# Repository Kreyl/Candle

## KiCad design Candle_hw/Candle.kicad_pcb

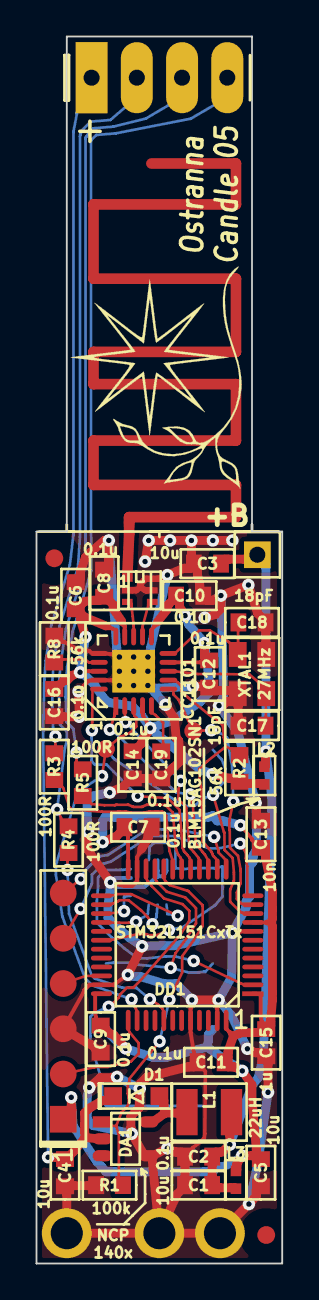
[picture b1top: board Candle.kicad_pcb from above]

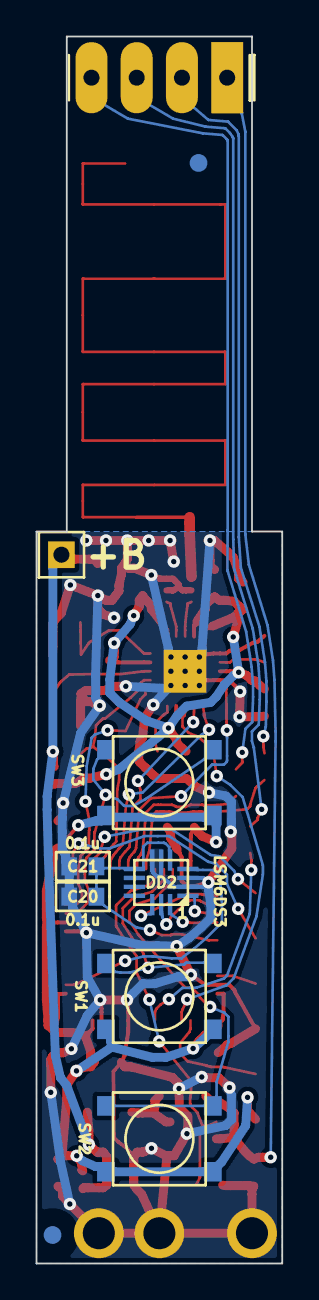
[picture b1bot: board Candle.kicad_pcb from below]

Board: 2 copper layers, 13.8 x 68.9 mm, 54 parts (8 on the bottom side), 39 nets.

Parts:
ANT1: ANT_PCB_MONO; ANT_868_10d4x36
BLN1: BALUN868JOHANSON; BALUN_JOHANSON868
C1, C3, C4, C5: 10u; CAP_0603
C2, C6, C7, C8, C9, C10, C11, C12, C14, C16, C19, C20, C21: 0.1u; CAP_0603
C13: 10n; CAP_0603
C15: 1u; CAP_0603
C17, C18: 18pF; CAP_0603
D1: BAT54WS; SOD323
DA1: NCP1400; SOT23-5
DD1: STM32L151CxTx; LQFP48
DD2: LSM6DS3; 14_3x2d5_p0d5
DD3: CC1101; QFN20
L1: 22uH; IND_1210_LQH32C
L2, L3: BLM15AG102SN1; IND_0402
Logo1: Logo; Ostranna_12d7_10d1
R1: 100k; RES_0603
R2, R8: 56k; RES_0603
R3, R4, R5: 100R; RES_0603
RP1, RP2, RP3, RP4: REFPOINT; REF_POINT_1MM
SW1, SW2, SW3: BUTTON; BTN_4x4_SMD
TP1, TP2: TESTPOINT; TESTPOINT_1MM
XL1: CONN_6; PLS-6-NoHole
XL2: CONN_1; PLS-1Square
XL3, XL4, XL5: CONN_1; SIL1_ROUND_1MM8
XL6: CONN_4; PLS-4-Long
XTAL1: 27MHz; 03225C4

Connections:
+3.3V: C4.2, D1.C, DA1.2, XL6.1
+BATT: C1.2, C2.2, C3.2, L1.2, L2.2, L3.2, XL2.1
/ACC_CS: DD1.25, DD2.12
/ACC_INT1: DD1.2, DD2.4
/ACC_MISO: DD1.27, DD2.1
/ACC_MOSI: DD1.28, DD2.14
/ACC_PWR: C20.1, C21.1, DD1.30, DD2.5, DD2.8
/ACC_SCK: DD1.26, DD2.13
/ANT1: ANT1.1, BLN1.1
/BLUE_LED: DD1.18, R5.2
/CC_CS: DD1.14, DD3.7, R2.1
/CC_GDO0: DD1.11, DD3.6, TP1.1
/CC_GDO2: DD1.38, DD3.3, TP2.1
/CC_MISO: DD1.16, DD3.2
/CC_MOSI: DD1.17, DD3.20
/CC_SCK: DD1.15, DD3.1
/GREEN_LED: DD1.41, R4.2
/LED_EN: DA1.1, DD1.20, R1.1
/Lout: D1.A, DA1.5, L1.1
/RED_LED: DD1.19, R3.2
/RF1: BLN1.4, DD3.12
/RF2: BLN1.3, DD3.13
/SWCLK: DD1.37, XL1.2
/SWDIO: DD1.34, XL1.4
/UART_RX: DD1.13, XL1.6
/UART_TX: DD1.12, XL1.5
GND: BLN1.2, BLN1.5, BLN1.6, C1.1, C2.1, C3.1, C4.1, C5.1, C6.2, C7.2, C8.2, C9.2, C10.2, C11.2, C12.2, C13.2, C14.2, C15.2, C16.2, C17.2, C18.2, C19.1, C20.2, C21.2, DA1.4, DD1.8, DD1.23, DD1.35, DD1.44, DD1.47, DD2.2, DD2.3, DD2.6, DD2.7, DD3.16, DD3.19, DD3.PAD, R1.2, R8.2, XL1.3, XL3.1, XL4.1, XL5.1, XTAL1.H
unnamed: C17.1, DD3.8, XTAL1.1
unnamed: C18.1, DD3.10, XTAL1.2
unnamed: C19.2, DD3.5
unnamed: DD1.10, SW3.1
unnamed: DD1.21, SW1.1
unnamed: DD1.22, SW2.1
unnamed: DD3.17, R8.1
unnamed: R3.1, XL6.2
unnamed: R4.1, XL6.3
unnamed: R5.1, XL6.4
PwrMCU: C5.2, C7.1, C9.1, C11.1, C13.1, C15.1, DD1.1, DD1.9, DD1.24, DD1.36, DD1.48, L3.1, SW1.2, SW2.2, SW3.2, XL1.1
VCC: C6.1, C8.1, C10.1, C12.1, C14.1, C16.1, DD3.4, DD3.9, DD3.11, DD3.14, DD3.15, DD3.18, L2.1, R2.2

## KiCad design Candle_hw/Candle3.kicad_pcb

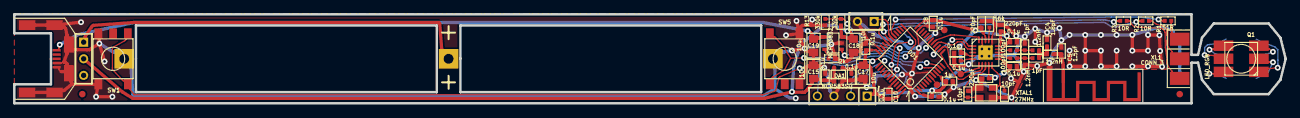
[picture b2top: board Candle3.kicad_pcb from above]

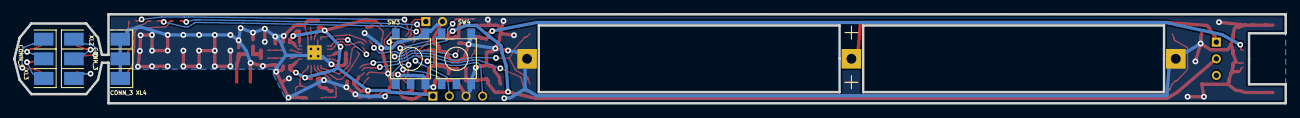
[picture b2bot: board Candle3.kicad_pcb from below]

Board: 2 copper layers, 194.4 x 13.6 mm, 63 parts (5 on the bottom side), 43 nets.

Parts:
ANT1: ANT_GENERAL; ANT_2400_MEANDER
C1, C3: 100pF; CAP_0402
C2, C6: 1pF; CAP_0402
C4: 1.8pF; CAP_0402
C5: 1.5pF; CAP_0402
C7, C13: 10pF; CAP_0402
C8, C9, C10, C11, C14, C16, C41, C51, C111, C141: 0.1u; CAP_0402
C12: 1u; CAP_0402
C15, C17, C18, C19: 10u; CAP_0805
C91, C151, C181: 220pF; CAP_0402
DA1: NCP583SQ; SC82AB
DA2: MCP73832; SOT23-5
DD1: STM32F100C4; LQFP48
DD2: CC2500; QFN20
L1, L2, L3: 1.2nH; IND_0402
Q1: LED_RGB; LED_HH5050_RGB
R1: 51R; RES_0402
R2, R3: 10R; RES_0402
R4: 2k; RES_0402
R6, R13: 330k; RES_0402
R171: 56k; RES_0402
RP1, RP2, RP3: REFPOINT; REF_POINT_1MM
SW1: SWITCH; SIL-3
SW2, SW3, SW4, SW5: BUTTON; BUTTON_6x6SMD
TP1, TP2: TESTPOINT; TESTPOINT_1MM
XL1, XL2, XL3, XL4: CONN_3; CONN_SOLDER3
XL5: ST_SWD; SIL-4
XL6: USB_MICRO_B; USBmicro_MOLEX_WM17142
XL7: CONN_2; SIL-2
XL9, XL15, XL16: CONN_1; SIL1_SQUARE_1MM5
XTAL1: 27MHz; CRYSTAL_03225C4

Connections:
+3.3V: C8.1, C9.1, C10.1, C11.1, C12.1, C16.1, C17.1, C41.1, C91.1, C111.1, C141.1, C151.1, C181.1, DA1.3, DD1.1, DD1.9, DD1.24, DD1.36, DD1.48, DD2.4, DD2.9, DD2.11, DD2.14, DD2.15, DD2.18, XL5.1
+5V: C19.1, DA2.4, XL6.1
+BATT: C14.1, C15.1, C18.1, DA1.1, DA1.4, DA2.3, R6.1, SW1.2
/Ant1: C1.1, DD2.12
/Ant2: C3.1, DD2.13
/BATTERY_PLUS: SW1.1, XL9.1
/BTN_DOWN: DD1.43, SW4.2
/BTN_PWR: DD1.10, SW2.2
/BTN_TX: DD1.11, SW5.2
/BTN_UP: DD1.42, SW3.2
/CC_CS: DD1.13, DD2.7
/CC_GDO0: DD1.14, DD2.6, TP1.1
/CC_MISO: DD1.16, DD2.2
/CC_MOSI: DD1.17, DD2.20
/CC_SCK: DD1.15, DD2.1
/Charge: DA2.1, DD1.25
/LED_B: DD1.32, R3.1
/LED_G: DD1.31, R2.1
/LED_R: DD1.29, R1.1
/SWCLK: DD1.37, XL5.2
/SWDIO: DD1.34, XL5.4
GND: ANT1.2, C4.2, C5.2, C6.2, C7.2, C8.2, C9.2, C10.2, C11.2, C12.2, C13.2, C14.2, C15.2, C16.2, C17.2, C18.2, C19.2, C41.2, C51.2, C91.2, C111.2, C141.2, C151.2, C181.2, DA1.2, DA2.2, DD1.8, DD1.23, DD1.35, DD1.44, DD1.47, DD2.16, DD2.19, DD2.PAD, L1.1, R4.2, R13.2, R171.2, SW2.1, SW3.1, SW4.1, SW5.1, XL4.1, XL4.2, XL4.3, XL5.3, XL6.4, XL6.5, XL6.SHLD, XL7.2, XL15.1, XL16.1, XTAL1.H
unnamed: DA2.5, R4.1
unnamed: Q1.RA, XL2.1
unnamed: Q1.GC, XL3.2
unnamed: Q1.RC, XL3.1
unnamed: Q1.BC, XL3.3
unnamed: Q1.GA, XL2.2
unnamed: Q1.BA, XL2.3
unnamed: R1.2, XL1.1
unnamed: R2.2, XL1.2
unnamed: R3.2, XL1.3
unnamed: C1.2, C2.1, L1.2
unnamed: DD1.7, TP2.1
unnamed: C3.2, C6.1, L3.2
unnamed: ANT1.1, C5.1, L2.1
unnamed: C2.2, C4.1, L2.2, L3.1
unnamed: DD1.30, XL7.1
unnamed: C13.1, DD2.10, XTAL1.2
unnamed: C7.1, DD2.8, XTAL1.1
unnamed: DD1.18, R6.2, R13.1
unnamed: DD2.17, R171.1
unnamed: C51.1, DD2.5

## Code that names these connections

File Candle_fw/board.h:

/*
 * board.h
 *
 *  Created on: 12 ñåíò. 2015 ã.
 *      Author: Kreyl
 */

#pragma once

#include <inttypes.h>

// ==== General ====
#define BOARD_NAME          "Candle05"
#define APP_NAME            "Candle_TxAcg"

// ==== High-level peripery control ====
#define BUTTONS_ENABLED         TRUE

#define SIMPLESENSORS_ENABLED   BUTTONS_ENABLED

// MCU type as defined in the ST header.
#define STM32L151xB

#define SYS_TIM_CLK         (Clk.APB1FreqHz)
#define I2C1_ENABLED        FALSE
#define I2C_USE_SEMAPHORE   FALSE
#define ADC_REQUIRED        FALSE

#if 1 // ========================== GPIO =======================================
// PortMinTim_t: GPIO, Pin, Tim, TimChnl, invInverted, omPushPull, TopValue
// UART
#define UART_GPIO       GPIOA
#define UART_TX_PIN     2
#define UART_RX_PIN     3

// LED
#define LED_EN_PIN      { GPIOB, 2, omPushPull }
#define LED_R_PIN       { GPIOB, 5, TIM3, 2, invInverted, omOpenDrain, 255 }
#define LED_G_PIN       { GPIOB, 0, TIM3, 3, invInverted, omOpenDrain, 255 }
#define LED_B_PIN       { GPIOB, 1, TIM3, 4, invInverted, omOpenDrain, 255 }

// Buttons
#define BTN_TX_PIN      GPIOA, 0, pudPullDown
#define BTN_UP_PIN      GPIOB, 10, pudPullDown
#define BTN_DOWN_PIN    GPIOB, 11, pudPullDown

#define BTN_TX_INDX     0
#define BTN_UP_INDX     1
#define BTN_DOWN_INDX   2

// Acc
#define ACG_IRQ_PIN     GPIOC, 13
#define ACG_CS_PIN      GPIOB, 12
#define ACG_SCK_PIN     GPIOB, 13, omPushPull, pudNone, AF5
#define ACG_MISO_PIN    GPIOB, 14, omPushPull, pudNone, AF5
#define ACG_MOSI_PIN    GPIOB, 15, omPushPull, pudNone, AF5
#define ACG_PWR_PIN     GPIOA, 9
#define ACG_SPI         SPI2

// Radio: SPI, PGpio, Sck, Miso, Mosi, Cs, Gdo0
#define CC_Setup0       SPI1, GPIOA, 5,6,7, 4, 1

#endif // GPIO

#if ADC_REQUIRED // ======================= Inner ADC ==========================
// Clock divider: clock is generated from the APB2
#define ADC_CLK_DIVIDER     adcDiv2

// ADC channels
//#define BAT_CHNL          1

#define ADC_VREFINT_CHNL    17  // All 4xx, F072 and L151 devices. Do not change.
#define ADC_CHANNELS        { ADC_VREFINT_CHNL }
#define ADC_CHANNEL_CNT     1   // Do not use countof(AdcChannels) as preprocessor does not know what is countof => cannot check
#define ADC_SAMPLE_TIME     ast96Cycles
#define ADC_SAMPLE_CNT      8   // How many times to measure every channel

#define ADC_SEQ_LEN         (ADC_SAMPLE_CNT * ADC_CHANNEL_CNT)

#endif

#if 1 // =========================== DMA =======================================
#define STM32_DMA_REQUIRED  TRUE
// ==== Uart ====
#define UART_DMA_TX_MODE(Chnl) (STM32_DMA_CR_CHSEL(Chnl) | DMA_PRIORITY_LOW | STM32_DMA_CR_MSIZE_BYTE | STM32_DMA_CR_PSIZE_BYTE | STM32_DMA_CR_MINC | STM32_DMA_CR_DIR_M2P | STM32_DMA_CR_TCIE)
#define UART_DMA_RX_MODE(Chnl) (STM32_DMA_CR_CHSEL(Chnl) | DMA_PRIORITY_MEDIUM | STM32_DMA_CR_MSIZE_BYTE | STM32_DMA_CR_PSIZE_BYTE | STM32_DMA_CR_MINC | STM32_DMA_CR_DIR_P2M | STM32_DMA_CR_CIRC)
#define UART_DMA_TX     STM32_DMA1_STREAM7
#define UART_DMA_RX     STM32_DMA1_STREAM6
#define UART_DMA_CHNL   2

// ==== ACG ====
#define ACG_DMA_TX      STM32_DMA1_STREAM5
#define ACG_DMA_RX      STM32_DMA1_STREAM4
#define ACG_DMA_CHNL    1

#if I2C1_ENABLED // ==== I2C ====
#define I2C1_DMA_TX     STM32_DMA1_STREAM6
#define I2C1_DMA_RX     STM32_DMA1_STREAM7
#endif

#if ADC_REQUIRED
#define ADC_DMA         STM32_DMA1_STREAM1
#define ADC_DMA_MODE    STM32_DMA_CR_CHSEL(0) |   /* dummy */ \
                        DMA_PRIORITY_LOW | \
                        STM32_DMA_CR_MSIZE_HWORD | \
                        STM32_DMA_CR_PSIZE_HWORD | \
                        STM32_DMA_CR_MINC |       /* Memory pointer increase */ \
                        STM32_DMA_CR_DIR_P2M |    /* Direction is peripheral to memory */ \
                        STM32_DMA_CR_TCIE         /* Enable Transmission Complete IRQ */
#endif // ADC

#endif // DMA

#if 1 // ========================== USART ======================================
#define PRINTF_FLOAT_EN FALSE
#define UART_TXBUF_SZ   1024
#define UART_RXBUF_SZ   99

#define UARTS_CNT       1

#define CMD_UART_PARAMS \
    USART2, UART_GPIO, UART_TX_PIN, UART_GPIO, UART_RX_PIN, \
    UART_DMA_TX, UART_DMA_RX, UART_DMA_TX_MODE(UART_DMA_CHNL), UART_DMA_RX_MODE(UART_DMA_CHNL)

#endif

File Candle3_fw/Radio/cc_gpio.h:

/*
 * cc_gpio.h
 *
 *  Created on: Nov 28, 2013
 *      Author: kreyl
 */

#ifndef CC_GPIO_H_
#define CC_GPIO_H_

// Pins
#define CC_GPIO     GPIOA
#define CC_GDO2     1
#define CC_GDO0     3
#define CC_SCK      5
#define CC_MISO     6
#define CC_MOSI     7
#define CC_CS       2

#if CC_GDO0 == 0
#define GDO0_IRQ_HANDLER     EXTI0_IRQHandler
#elif CC_GDO0 == 1
#define GDO0_IRQ_HANDLER     EXTI1_IRQHandler
#elif CC_GDO0 == 2
#define GDO0_IRQ_HANDLER     EXTI2_IRQHandler
#elif CC_GDO0 == 3
#define GDO0_IRQ_HANDLER     EXTI3_IRQHandler
#elif CC_GDO0 == 4
#define GDO0_IRQ_HANDLER     EXTI4_IRQHandler
#endif

// SPI
#define CC_SPI      SPI1

#endif /* CC_GPIO_H_ */

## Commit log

2016-02-22 Attiny45
2016-02-22 Candle3
2016-02-22 Candle 868 MHz
2017-03-26 Copy of Locket
2017-03-30 + Candle04 sent to production
2017-04-07 Antenna matched
2017-04-08 + FW
2017-04-08 Periphery seems operational
2017-04-08 Prerelease (rf power adjustment required)
2018-01-04 FeelEachOther Release
2018-04-14 Proceeding
2018-04-14 Proceeding with os
2018-04-14 Switch to newer os ok, compiled ok
2018-04-14 + Buttons work
2018-04-14 Correct buttons work
2018-04-14 * Buttons are even better
2018-04-14 GetPrev in ColorTable
2018-04-15 Switch to HSV
2018-04-15 State Machine works properly
2018-04-15 + PwrDown ok RC
2018-04-15 + RCHNL + TX Black when off
2018-10-13 + Candle05 hw
2018-11-30 + Fw for HW 5 UART works
2018-12-02 Release
2018-12-19 ACG and btn tx ok
